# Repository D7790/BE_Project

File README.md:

# Wattsense

Battery-mounted, battery-powered monitoring and advice using remaining-energy/runtime estimates and known AC/DC load signatures.

**Current scope — clarified 3 October 2026:** Start with [the battery-centred scope](docs/BATTERY_CENTRED_SCOPE.md). WattSense mounts near the battery and runs from a regulated battery supply. It estimates remaining charge, usable energy and runtime, then recommends which optional loads to turn off using known signatures and user priorities. Solar or a compatible AC-to-DC charger charges the battery; DC loads use converters and AC loads use an inverter. Random Forest is a candidate to compare with a Decision Tree and feature baseline; no measured signatures or classifier accuracy exist yet.

**Current Review 3 presentation:** [Editable 14-slide battery-centred deck](output/pptx/WattSense_Review_3_Battery_Centred_Final.pptx). It presents the battery-powered monitor/adviser, AC/DC load paths, charging options, confirmed team details and 20 literature titles. It supersedes the standalone AC-first scope.

**Existing foundation:** The [30 September project and paper audit](docs/RECHECK_2026-09-30.md) records checks of the small DC implementation. The [earlier buying/build checklist](docs/NEXT_STEPS.md), research paper and team guides describe that narrower scope. The [paper guide](paper/READ_ME_FIRST.md) links the retained PDF and editable Word companion; these documents need follow-up narrative alignment before reuse for the expanded project.

This folder now contains a runnable local dashboard, a development simulator, a USB-serial collector, timestamped CSV logging, ESP32 firmware, automated software tests and hardware implementation notes.

**DC foundation PCB:** `hardware/pcb/wattsense-main-revB-4layer/` contains revision B: a routed four-layer KiCad board with two internal ground planes, updated I2C pull-ups, prototype fabrication exports, BOM and assembly guide. Its 2 A battery-side and 1.5 A continuous 5 V project ceilings need physical qualification. It cannot connect to mains or carry household-inverter battery current. The original two-layer revision A remains in `hardware/pcb/wattsense-main/` as a historical alternative. Do not mix their BOMs/exports. Physical assembly and delivered pricing remain pending.

**DC foundation simulation results:** `docs/SIMULATION_REPORT.md` contains the 28 September tests, reduced SPICE results, runtime comparison and limitations. Run `run_simulations.ps1` to reproduce the suite; figures and raw data are in `simulations/results/`. They do not validate the proposed AC measurement or signature stage.

**Retained DC hardware-performance models:** [Results, startup limitations and smaller starter loads](docs/HARDWARE_PERFORMANCE.md), plus [the earlier DC flow](docs/PROJECT_FLOW.md), include actual PCB path geometry, assumed electrical losses, 18 paired runtime scenarios and six additional ngspice startup cases. With the stated 2.5 W starter loads, the model predicts 5.48 h versus 7.88 h of lamp service; these are simulated DC results. The recorded full suite contains 45 Python tests and 67 C++ assertions.

**Next practical steps:** Qualify battery-powered monitoring, complete the needed data path and collect known-load profiles using [the battery-centred plan](docs/BATTERY_CENTRED_SCOPE.md). Larger inverter setups need whole-battery sensing rated for their current; the 2 A Rev B path is unsuitable. The below-₹10,000 target is unchanged; the earlier ₹9,700 DC allocation excludes added inverter/AC equipment, so delivered affordability needs a complete quote or borrowing plan. The [Pune buying plan](hardware/BUYING_PLAN_PUNE.md), [supplier questions](hardware/SUPPLIER_QUESTIONS.md) and [first lab session](docs/LAB_START_GUIDE.md) remain DC foundation resources. A separate `bringup` firmware build keeps the fan off while reporting raw sensors. The `calibration/` folder contains a blank lab worksheet and explicitly simulated examples; no real measurements have been recorded.

**Earlier cross-check completed:** [Review findings and remaining physical tests](docs/CROSSCHECK_REPORT.md). Corrected 10 Hz firmware accumulation precision, malformed serial handling, calibration safeguards and conflicting lab instructions. That checkpoint passed 37 Python tests, 67 native C++ assertions, both ESP32 builds and refreshed CAD audits. The newer hardware model adds eight Python tests; native CAD is unchanged.

**There is no physical prototype yet. Simulator values are illustrative and must not be presented as experimental results. The firmware's physical output is disabled by default.**

## Start the DC foundation demonstration

This runnable demo illustrates the existing battery/runtime and priority-control foundation. Household AC measurement and signature recognition are planned additions and are not demonstrated by it.

From this project folder in PowerShell:

    .\.venv\Scripts\python.exe -m wattsense.server --mode simulated

Open http://127.0.0.1:8765 in a browser. If it is already running, just open that address. You can also run run_demo.ps1 or double-click run_demo.cmd.

Press Ctrl+C to stop a terminal-launched server. The background demo started during project setup can be stopped with stop_demo.ps1; the script checks the recorded process identity before stopping it. CSV records are flushed throughout the session.

The simulator needs only Python 3.10 or newer. On another computer without the supplied local environment:

    python -m wattsense.server --mode simulated

The server listens only on this computer. No cloud service, account or API key is required.

### Try these actions

1. Normal load: view the illustrative charge, power and runtime.
2. Limited backup: wait about four seconds and observe the optional load switch off.
3. Restore fan: the controller refuses restoration when the predicted full-load runtime is too short.
4. Solar charging: battery current becomes negative. The no-future-charge runtime heuristic excludes future solar input.
5. Sensor disconnected: charge/runtime become unknown and the optional load switches off.
6. Export session CSV: save the data with its simulated/hardware source label.

Resetting a scenario establishes a new simulated reference and clears the visible chart. The full session CSV retains earlier records; scenario resets appear as device-uptime discontinuities and are documented in the on-screen event log. The simulator uses real elapsed time, not accelerated battery discharge.

## Use physical hardware later

Read hardware/REFERENCE_WIRING.md and firmware/README.md before connecting a battery.

Create/install dependencies if needed:

    python -m venv .venv
    .\.venv\Scripts\python.exe -m pip install -r requirements.txt
    .\.venv\Scripts\python.exe -m wattsense.server --list-ports

Start hardware mode with the actual serial port:

    .\.venv\Scripts\python.exe -m wattsense.server --mode hardware --serial-port COM5

COM5 is an example. Hardware mode does not fall back to simulated data when a sensor or serial connection is missing. The dashboard is read-only in hardware mode. The ESP32 handles physical load decisions independently of the computer.

Close the dashboard's hardware server before opening the same port in a serial terminal or uploading firmware. Opening an ESP32 serial connection can reset the board; charge starts unknown after each reboot.

## Build firmware

    .\.venv\Scripts\python.exe -m pip install -r requirements-build.txt
    .\build_firmware.ps1

build_firmware.ps1 runs the build using the project environment. It creates a short Windows junction at your user profile's .ws-pio pointing to this project's .local/platformio cache. This avoids compiler process/path failures in the longer workspace path; package files stay in the project. The script refuses to overwrite an unrelated path. Building does not flash a board.

The reference target is a classic ESP32 development board with GPIO21/22 available for I2C, not an ESP32-C3/S3 board. Exact module and board compatibility must be checked before wiring or uploading. GPIO27 provides local load control, and a separate GPIO26 button permits full-reference confirmation while the dashboard remains connected.

## Run software tests

    .\.venv\Scripts\python.exe -m unittest discover -s tests -v

Tests cover the reference estimator, charge/discharge sign, reserve handling, measurement gaps, load restoration, simulator scenarios, serial message validation, logging and the HTTP interface. Software tests do not establish physical battery accuracy.

## Folder map

| Path | Purpose |
| --- | --- |
| docs/BATTERY_CENTRED_SCOPE.md | Current battery-powered monitor/adviser scope, AC/DC loads, charging and development plan |
| docs/EXPANDED_SCOPE_AC_DC.md | Superseded standalone AC-first plan; retained for history |
| wattsense/model.py | Simulator reference estimator and control policy |
| wattsense/simulator.py | Illustrative battery/load/solar model |
| wattsense/server.py | Local server, serial collector and CSV recorder |
| web/ | Dashboard interface, with no external assets or CDN dependency |
| firmware/ | PlatformIO ESP32 firmware and configuration |
| hardware/REFERENCE_WIRING.md | Power paths, signal assignments and assembly checks |
| hardware/BOM.md | Buying specification and provisional budget |
| hardware/PCB_REQUIREMENTS.md | PCB design status and physical validation criteria |
| hardware/pcb/wattsense-main-revB-4layer/ | Current four-layer revision B, KiCad sources, prototype fabrication files and checks |
| hardware/pcb/wattsense-main/ | Preserved two-layer revision A budget alternative |
| simulations/ | Reproducible SPICE, host C++ tests, plant runs and figures |
| docs/REVIEW_DEMO.md | Review demonstration and completed/pending claims |
| docs/TEST_PLAN.md | Physical validation procedures and blank results tables |
| docs/PROTOCOL.md | Serial telemetry format and sign conventions |
| tests/ | Automated software tests |
| logs/ | Local CSV session recordings, ignored by Git |
| WATTSENSE_PROJECT_BLUEPRINT.md | Historical DC foundation blueprint, superseded by the expanded roadmap |

## Current limitations

- Hardware has not been assembled, calibrated or tested.
- The final battery-powered device, complete whole-battery sensing path and larger compatible backup setup remain to be qualified. Any supporting AC meter must use a documented isolated data interface and enclosed test arrangement.
- No measured appliance-signature dataset, raw AC logger, trained classifier or validated UNKNOWN rule exists yet. Random Forest is an initial candidate, not an achieved model result.
- The current INA219/DC board and serial protocol do not acquire AC real power, RMS values or power factor. A new meter adapter and data path are required.
- Known-load energy attribution, recommendation benefit and backup-runtime errors have not been evaluated. Aggregate load combinations are a later milestone; similar profiles may remain ambiguous.
- The historical ₹9,700 DC allocation excludes the added AC and household backup equipment; the expanded budget is unconfirmed.
- Pack capacity, efficiency and temperature/voltage limits are provisional.
- The retained DC firmware requires a verified manual charge reference; automatic full-charge detection is not implemented.
- Temperature is measured at the battery surface, not inside cells.
- The DC foundation's runtime uses remaining charge times nominal voltage, with a configured reserve. Its no-future-charge heuristic uses load-branch power and omits some upstream losses; it is not a guaranteed minimum runtime and requires evaluation against actual discharge runs. The household AC backup estimator is a planned separate extension.
- The DC simulator mirrors the existing priority policy; ESP32 firmware additionally checks its hardware lock and voltage limits. Tests of the Python model are not execution tests of the ESP32 binary.
- In the retained DC demonstrator, the essential load is not individually metered. Optional-load status reports the controller command; there is no independent relay-contact feedback. This is not an implemented household AC switching system.
- Appliance recognition is now part of the planned expanded scope. Cloud services and a mobile app are optional; no such integration is implemented. The retained DC CAD/fabrication files are engineering prototype designs awaiting physical validation.
- BMS and charger protections remain necessary. The ESP32 is not the pack's safety BMS.

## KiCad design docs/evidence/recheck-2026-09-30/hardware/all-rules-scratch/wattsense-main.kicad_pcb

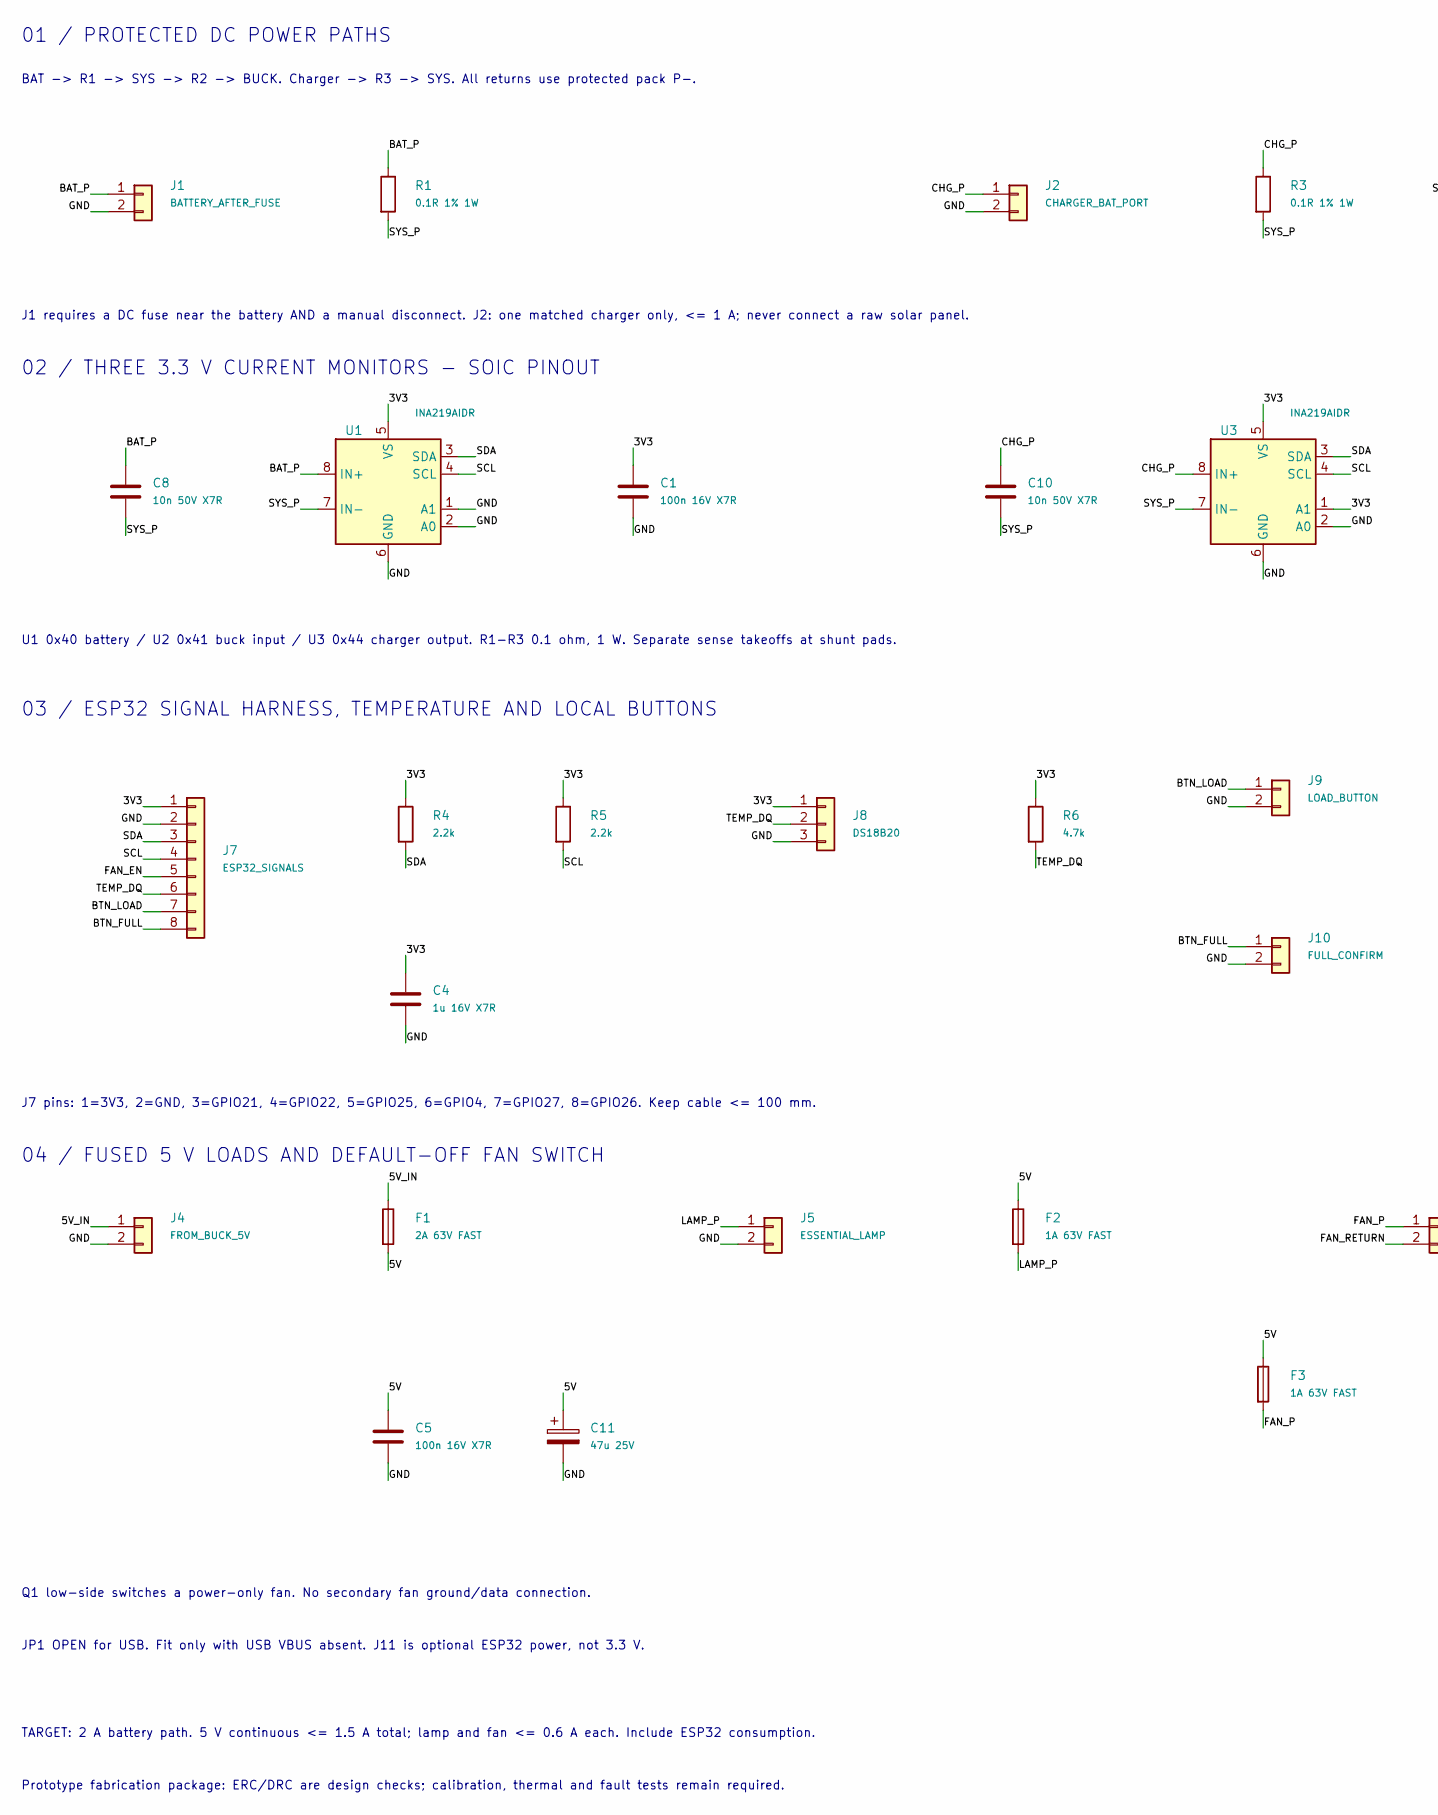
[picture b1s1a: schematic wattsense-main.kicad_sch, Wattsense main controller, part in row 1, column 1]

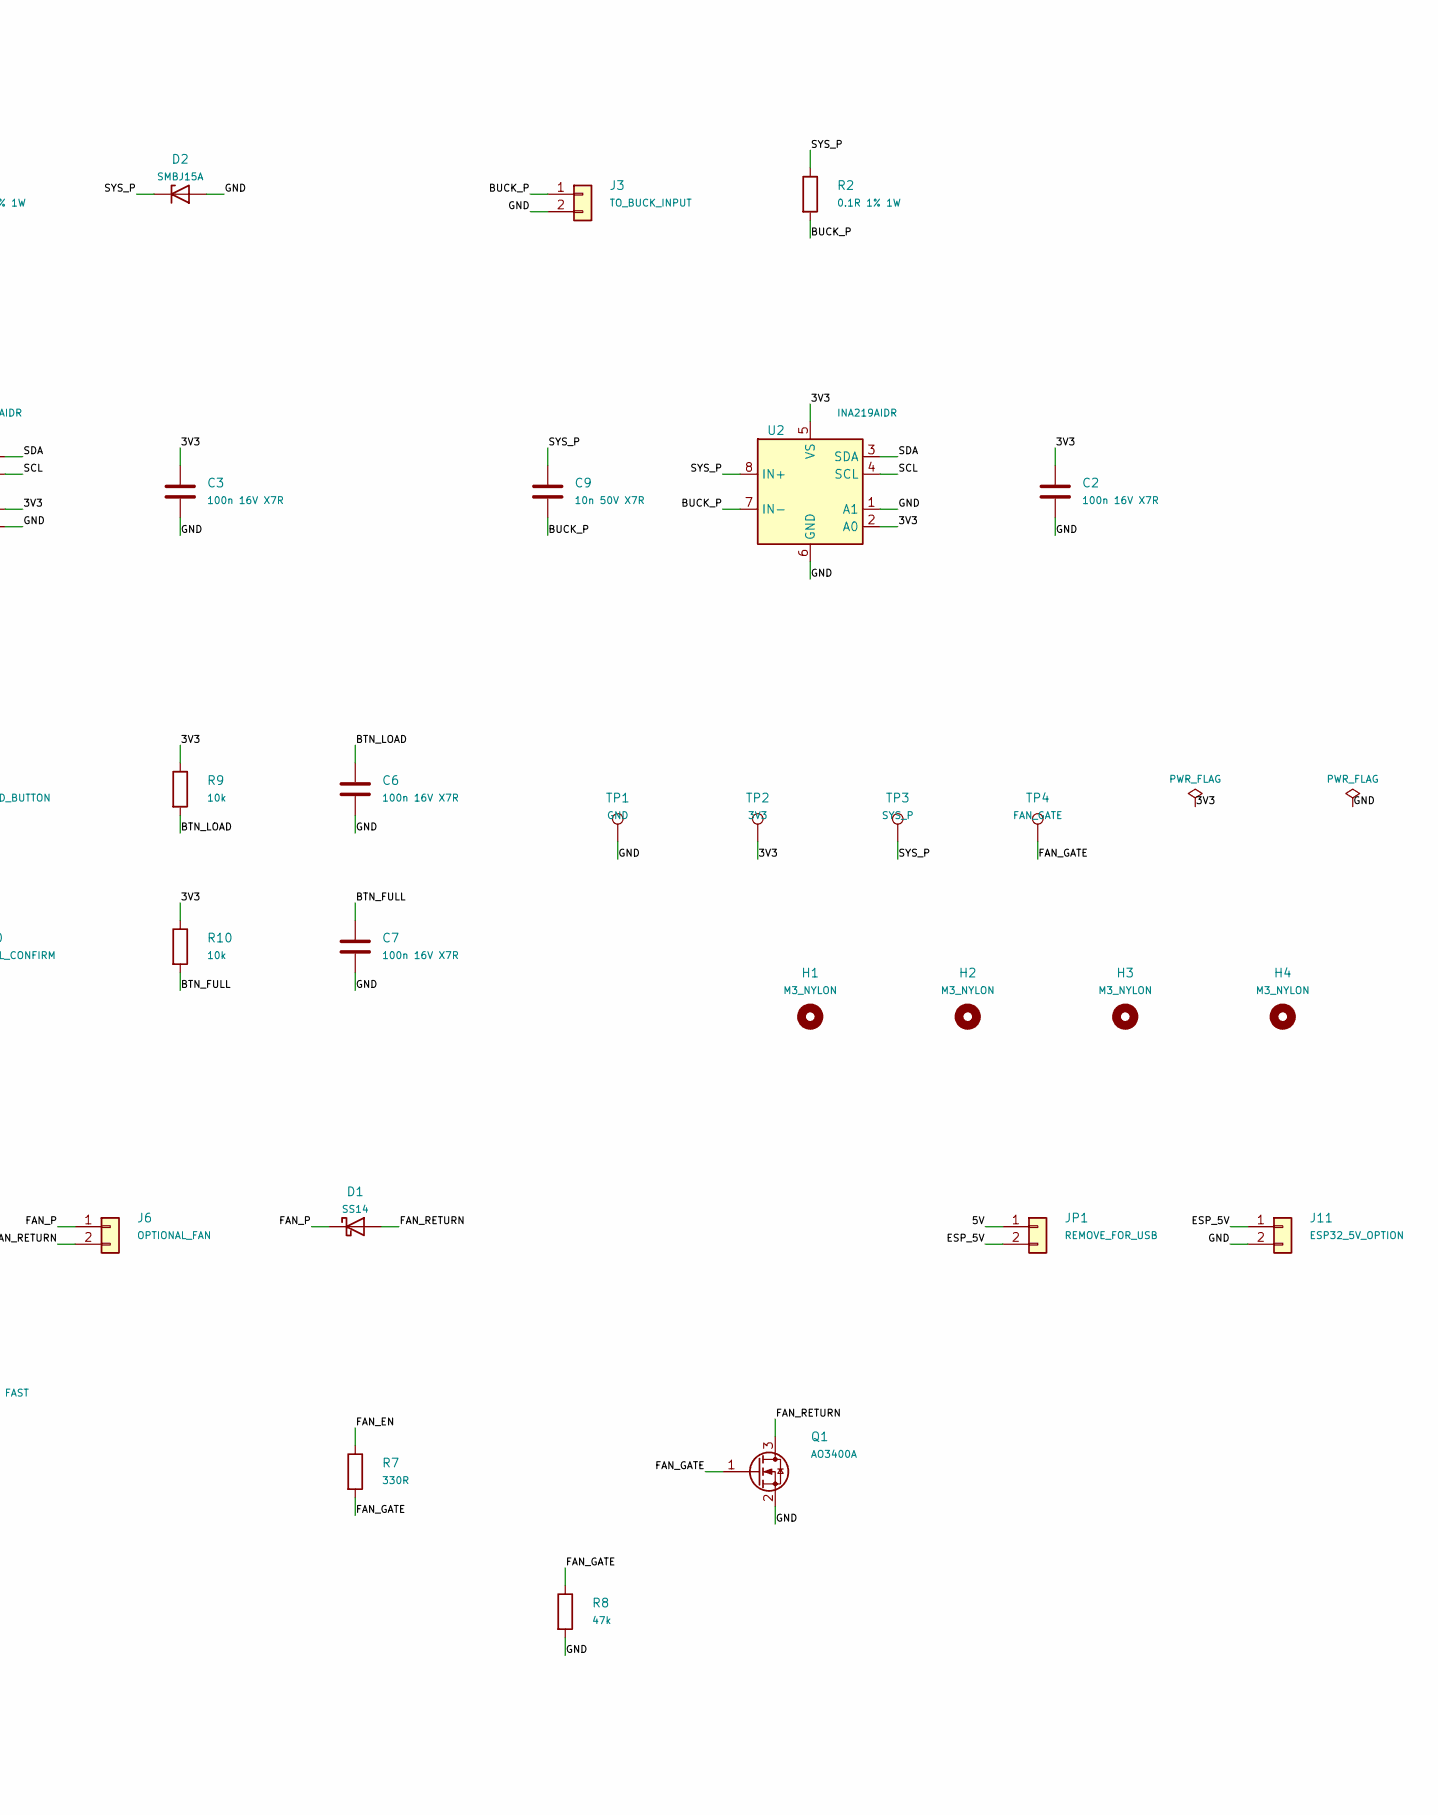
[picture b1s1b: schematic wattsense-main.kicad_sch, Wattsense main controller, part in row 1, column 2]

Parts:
C1, C2, C3, C5, C6, C7: 100n 16V X7R; C_0805_2012Metric_Pad1.18x1.45mm_HandSolder
C4: 1u 16V X7R; C_0805_2012Metric_Pad1.18x1.45mm_HandSolder
C8, C9, C10: 10n 50V X7R; C_0805_2012Metric_Pad1.18x1.45mm_HandSolder
C11: 47u 25V; CP_Radial_D5.0mm_P2.00mm
D1: SS14; D_SMA
D2: SMBJ15A; D_SMB
F1: 2A 63V FAST; Fuse_1206_3216Metric_Pad1.42x1.75mm_HandSolder
F2, F3: 1A 63V FAST; Fuse_1206_3216Metric_Pad1.42x1.75mm_HandSolder
H1, H2, H3, H4: M3_NYLON; MountingHole_3.2mm_M3
J1: BATTERY_AFTER_FUSE; TerminalBlock_Phoenix_MKDS-1,5-2-5.08_1x02_P5.08mm_Horizont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
J2: CHARGER_BAT_PORT; TerminalBlock_Phoenix_MKDS-1,5-2-5.08_1x02_P5.08mm_Horizont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
J3: TO_BUCK_INPUT; TerminalBlock_Phoenix_MKDS-1,5-2-5.08_1x02_P5.08mm_Horizont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
J4: FROM_BUCK_5V; TerminalBlock_Phoenix_MKDS-1,5-2-5.08_1x02_P5.08mm_Horizont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
J5: ESSENTIAL_LAMP; TerminalBlock_Phoenix_MKDS-1,5-2-5.08_1x02_P5.08mm_Horizont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
J6: OPTIONAL_FAN; TerminalBlock_Phoenix_MKDS-1,5-2-5.08_1x02_P5.08mm_Horizont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
J7: ESP32_SIGNALS; PinHeader_1x08_P2.54mm_Vertical
J8: DS18B20; PinHeader_1x03_P2.54mm_Vertical
J9: LOAD_BUTTON; PinHeader_1x02_P2.54mm_Vertical
J10: FULL_CONFIRM; PinHeader_1x02_P2.54mm_Vertical
J11: ESP32_5V_OPTION; PinHeader_1x02_P2.54mm_Vertical
JP1: REMOVE_FOR_USB; PinHeader_1x02_P2.54mm_Vertical
Q1: AO3400A; SOT-23
R1, R2, R3: 0.1R 1% 1W; R_2512_6332Metric_Pad1.40x3.35mm_HandSolder
R4, R5: 2.2k; R_0805_2012Metric_Pad1.20x1.40mm_HandSolder
R6: 4.7k; R_0805_2012Metric_Pad1.20x1.40mm_HandSolder
R7: 330R; R_0805_2012Metric_Pad1.20x1.40mm_HandSolder
R8: 47k; R_0805_2012Metric_Pad1.20x1.40mm_HandSolder
R9, R10: 10k; R_0805_2012Metric_Pad1.20x1.40mm_HandSolder
TP1: GND; TestPoint_Pad_D2.0mm
TP2: 3V3; TestPoint_Pad_D2.0mm
TP3: SYS_P; TestPoint_Pad_D2.0mm
TP4: FAN_GATE; TestPoint_Pad_D2.0mm
U1, U2, U3: INA219AIDR; SOIC-8_3.9x4.9mm_P1.27mm

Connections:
/3V3: C1.1, C2.1, C3.1, C4.1, J7.1, J8.1, R4.1, R5.1, R6.1, R9.1, R10.1, TP2.1, U1.5 (VS), U2.2 (A0), U2.5 (VS), U3.1 (A1), U3.5 (VS)
/5V: C5.1, C11.1, F1.2, F2.1, F3.1, JP1.1
/5V_IN: F1.1, J4.1
/BAT_P: C8.1, J1.1, R1.1, U1.8 (IN+)
/BTN_FULL: C7.1, J7.8, J10.1, R10.2
/BTN_LOAD: C6.1, J7.7, J9.1, R9.2
/BUCK_P: C9.2, J3.1, R2.2, U2.7 (IN-)
/CHG_P: C10.1, J2.1, R3.1, U3.8 (IN+)
/ESP_5V: J11.1, JP1.2
/FAN_EN: J7.5, R7.1
/FAN_GATE: Q1.1 (G), R7.2, R8.1, TP4.1
/FAN_P: D1.1 (K), F3.2, J6.1
/FAN_RETURN: D1.2 (A), J6.2, Q1.3 (D)
/GND: C1.2, C2.2, C3.2, C4.2, C5.2, C6.2, C7.2, C11.2, D2.2 (A), J1.2, J2.2, J3.2, J4.2, J5.2, J7.2, J8.3, J9.2, J10.2, J11.2, Q1.2 (S), R8.2, TP1.1, U1.1 (A1), U1.2 (A0), U1.6 (GND), U2.1 (A1), U2.6 (GND), U3.2 (A0), U3.6 (GND)
/LAMP_P: F2.2, J5.1
/SCL: J7.4, R5.2, U1.4 (SCL), U2.4 (SCL), U3.4 (SCL)
/SDA: J7.3, R4.2, U1.3 (SDA), U2.3 (SDA), U3.3 (SDA)
/SYS_P: C8.2, C9.1, C10.2, D2.1 (K), R1.2, R2.1, R3.2, TP3.1, U1.7 (IN-), U2.8 (IN+), U3.7 (IN-)
/TEMP_DQ: J7.6, J8.2, R6.2

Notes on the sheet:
01 / PROTECTED DC POWER PATHS
BAT -> R1 -> SYS -> R2 -> BUCK. Charger -> R3 -> SYS. All returns use protected pack P-.
J1 requires a DC fuse near the battery AND a manual disconnect. J2: one matched charger only, <= 1 A; never connect a raw solar panel.
02 / THREE 3.3 V CURRENT MONITORS - SOIC PINOUT
U1 0x40 battery / U2 0x41 buck input / U3 0x44 charger output. R1-R3 0.1 ohm, 1 W. Separate sense takeoffs at shunt pads.
03 / ESP32 SIGNAL HARNESS, TEMPERATURE AND LOCAL BUTTONS
J7 pins: 1=3V3, 2=GND, 3=GPIO21, 4=GPIO22, 5=GPIO25, 6=GPIO4, 7=GPIO27, 8=GPIO26. Keep cable <= 100 mm.
04 / FUSED 5 V LOADS AND DEFAULT-OFF FAN SWITCH
Q1 low-side switches a power-only fan. No secondary fan ground/data connection.
JP1 OPEN for USB. Fit only with USB VBUS absent. J11 is optional ESP32 power, not 3.3 V.
TARGET: 2 A battery path. 5 V continuous <= 1.5 A total; lamp and fan <= 0.6 A each. Include ESP32 consumption.
Prototype fabrication package: ERC/DRC are design checks; calibration, thermal and fault tests remain required.

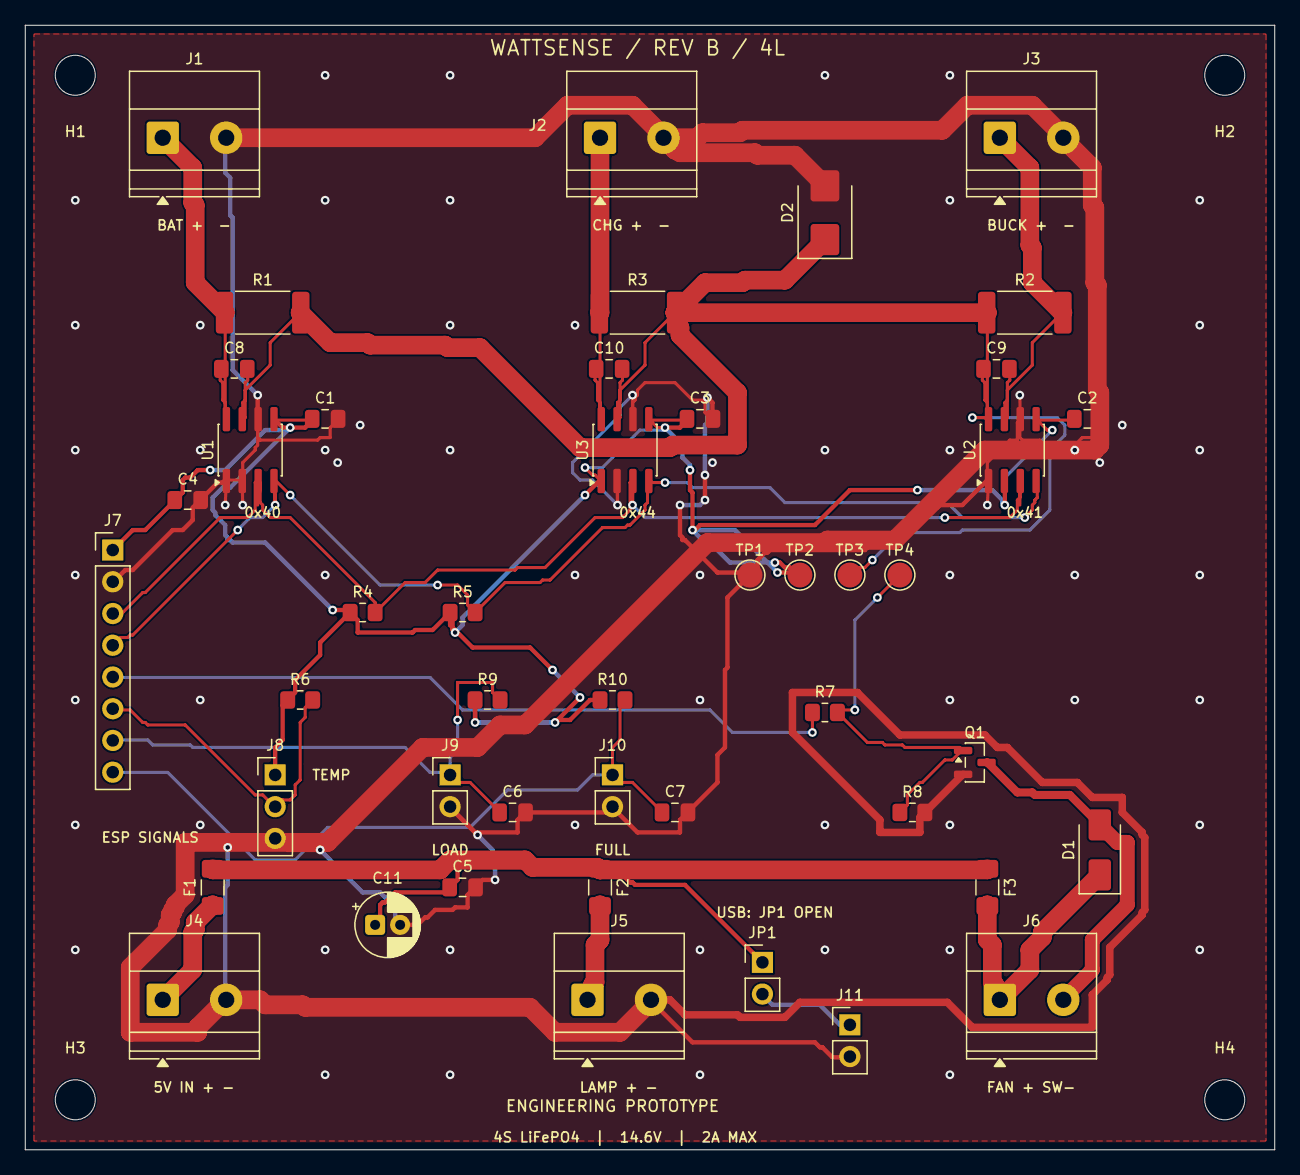
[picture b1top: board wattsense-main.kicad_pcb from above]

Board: 4 copper layers, 100.0 x 90.0 mm, 50 parts (0 on the bottom side), 19 nets.

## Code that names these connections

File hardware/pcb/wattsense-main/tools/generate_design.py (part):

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    add(f'C{i}','100n 16V X7R','Device','C',C0805,{1:'3V3',2:'GND'},(x+5,81.5),(schx+35.56,81.28),mpn='GRM21BR71C104KA01L')
    add(f'C{i+7}','10n 50V X7R','Device','C',C0805,{1:plus,2:minus},(x-2.27,77.5),(schx-38.1,81.28),mpn='GRM21BR71H103KA01L',note='Differential input capacitor; no shared high-current sense routing.')

add('J7','ESP32_SIGNALS','Connector_Generic','Conn_01x08',HDR(8),dict(enumerate(['3V3','GND','SDA','SCL','FAN_EN','TEMP_DQ','BTN_LOAD','BTN_FULL'],1)),(57,92),(38.1,134.62),note='Cable to classic ESP32; pin map in assembly guide. 3V3 is input from ESP32.')
add('J8','DS18B20','Connector_Generic','Conn_01x03',HDR(3),{1:'3V3',2:'TEMP_DQ',3:'GND'},(70,110),(129.54,129.54),note='Powered 3-wire temperature probe; verify probe wire mapping.')
add('J9','LOAD_BUTTON','Connector_Generic','Conn_01x02',HDR(2),{1:'BTN_LOAD',2:'GND'},(84,110),(195.58,124.46),note='External normally-open momentary button.')
add('J10','FULL_CONFIRM','Connector_Generic','Conn_01x02',HDR(2),{1:'BTN_FULL',2:'GND'},(97,110),(195.58,147.32),note='External normally-open button; hold 5 s only after verified full charge.')
for ref,val,nets,xy,sch,mpn in [
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 ('C7','100n 16V X7R',{1:'BTN_FULL',2:'GND'},(102,113),(254,147.32)),
]: add(ref,val,'Device','C',C0805,nets,xy,sch,note='0805 ceramic; specified voltage is minimum.')
add('C11','47u 25V','Device','C_Polarized','Capacitor_THT:CP_Radial_D5.0mm_P2.00mm',{1:'5V',2:'GND'},(78,122),(91.44,218.44),mpn='Panasonic EEU-FR1E470',note='Observe polarity; verify 5 mm diameter / 2 mm lead pitch.')
add('Q1','AO3400A','Transistor_FET','AO3400A','Package_TO_SOT_SMD:SOT-23',{1:'FAN_GATE',2:'GND',3:'FAN_RETURN'},(126,109),(312.42,223.52),mpn='AO3400A',note='Low-side switch, 3.3 V gate; pin 1 G, 2 S, 3 D.')
add('D1','SS14','Device','D_Schottky','Diode_SMD:D_SMA',{1:'FAN_P',2:'FAN_RETURN'},(136,116),(254,187.96),rot=90,mpn='SS14-E3/61T',note='Flyback: cathode stripe to fan positive.')
add('D2','SMBJ15A','Device','D_Zener','Diode_SMD:D_SMB',{1:'SYS_P',2:'GND'},(114,65),(228.6,38.1),rot=90,mpn='SMBJ15A-E3/52',note='Unidirectional TVS, cathode to SYS_P. Does not provide reverse-polarity protection.')
for ref,val,nets,xy,sch,mpn in [
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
